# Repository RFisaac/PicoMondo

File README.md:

# PicoMondo

RP2350B control board for museum and maker exhibits (Clark Planetarium), designed in KiCad 10.

- `kicad/` is the project (`picomondo.kicad_pro`). Start with `kicad/README.md` and `kicad/DECISIONS.md`.
- `kicad/tools/` holds the Python scripts that generate and check the schematic and board.

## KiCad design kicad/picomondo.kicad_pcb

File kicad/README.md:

# PicoMondo KiCad project

Open `picomondo.kicad_pro` in KiCad 10. See [DECISIONS.md](DECISIONS.md) for what has been decided.
Reference designs and source material are in `../resources/`.

## Status

| Sheet | File | State |
|-------|------|-------|
| MCU core (RP2350B, regulator, crystal, flash, boot/reset, USB resistors, SWD) | `mcu_core.kicad_sch` | Done; all 80 MCU pin connections match the Pi minimal design |
| 5 V buck-boost (TPS55288) | `power_buck.kicad_sch` | Done, ERC clean (docs/power_buck_boost.md) |
| Power input (diode-OR, fuse, TVS, connectors) | `power_input.kicad_sch` | Done (docs/power_input.md) |
| 3.3 V regulators (AP2112K x2) | `power_ldo.kicad_sch` | Done (docs/power_ldo.md) |
| Switched outputs J7 / J8 / +5V_SW | `power_outputs.kicad_sch` | Done (docs/power_outputs.md) |
| USB-C + PD controller (STUSB4500) | `usb_pd.kicad_sch` | Done (docs/usb_pd.md) |
| EdgeLock connectors J1-J6, J9 | `io_edgelock.kicad_sch` | Done; real Molex footprints incl. board-edge notches (docs/io.md) |
| GPIO indicator LEDs | `io_indicators.kicad_sch` | Done |
| Arduino and Pico sockets | `io_headers.kicad_sch` | Done |
| microSD, WS2812, LEDs, pull-ups, test points, mounting | `io_misc.kicad_sch` | Done |
| PCB | `picomondo.kicad_pcb` | Created: outline, EdgeLock edge connectors, mounting holes, Arduino/Pico sockets placed; all parts imported, rest staged for you to place and route (docs/pcb.md) |

## How the schematic is built

Every part is placed explicitly and every connection is a pin stub ending in a net label or power
symbol, so net names (not wire routing) define the connections. GPIO, `RUN`, `USB_D+/-` and power
nets are global and join across sheets; other labels are local to their sheet.

`tools/` holds the generator and checkers:

| Script | Purpose |
|--------|---------|
| `build.py` | Creates the initial project files. **Overwrites** the schematics: do not run after editing in KiCad. |
| `kihelp.py`, `sheet_*.py` | Helper library and per-sheet definitions |
| `erc_report.py` | Runs KiCad ERC and prints a summary |
| `netlist.py` | Exports the netlist; `--ref U1`, `--net +3V3`, `--nets` |
| `compare_pi.py`, `compare_passives.py` | Check the MCU core against the Raspberry Pi reference |
| `make_pcb.py` | Creates the PCB once (needs KiCad's Python); see docs/pcb.md |
| `drc_report.py`, `project_settings.py` | PCB DRC summary; design rules and net classes |
| `place_edgelock_resistors.py` | Put each EdgeLock 100 ohm resistor in line with its pin |
| `place_swd_switches.py` | Place SWD header and BOOTSEL/RESET buttons at the right edge |
| `arrange_offboard.py` | Lay out the parts still off the board as labelled sub-circuit clusters |
| `place_rest.py` | Fit the remaining off-board parts into free space, near the parts they connect to |
| `place_usb_pd.py` | Place the USB-C PD support parts at J13 / U10 |
| `tp_to_back.py` | Flip the test points to the back |
| `place_mcu.py` | Place the RP2350B with its decoupling, regulator, crystal, flash and USB resistors |
| `place_gpio_indicators.py` | Continue each EdgeLock column with its 470 ohm and LED (LED beside the resistor, in an L) |
| `remove_led_jumpers.py` | Removed the ADC LED solder jumpers (schematic and board) |
| `add_shield_outlines.py` | Non-printing Uno and Pico outlines in the socket group |
| `apply_parts.py`, `sync_board_parts.py`, `bom.py` | LCSC numbers from `bom/parts.csv` into schematic and board; JLCPCB BOM, CPL and stock report |
| `fetch_datasheets.py`, `make_edgelock_fp.py`, `fix_lcsc_footprints.py`, `symfind.py`, `libpins.py` | Library and datasheet helpers |

Once a sheet has been edited in KiCad, that file is the source of truth. New sheets can be added
with the generator; edits to existing sheets should be made in KiCad or with kiutils
read-modify-write.

## Known ERC output

- `isolated_pin_label` on `GPIOn`: expected until the IO sheets exist.
- `lib_symbol_mismatch` on the crystal and flash: embedded copies differ cosmetically from the library.

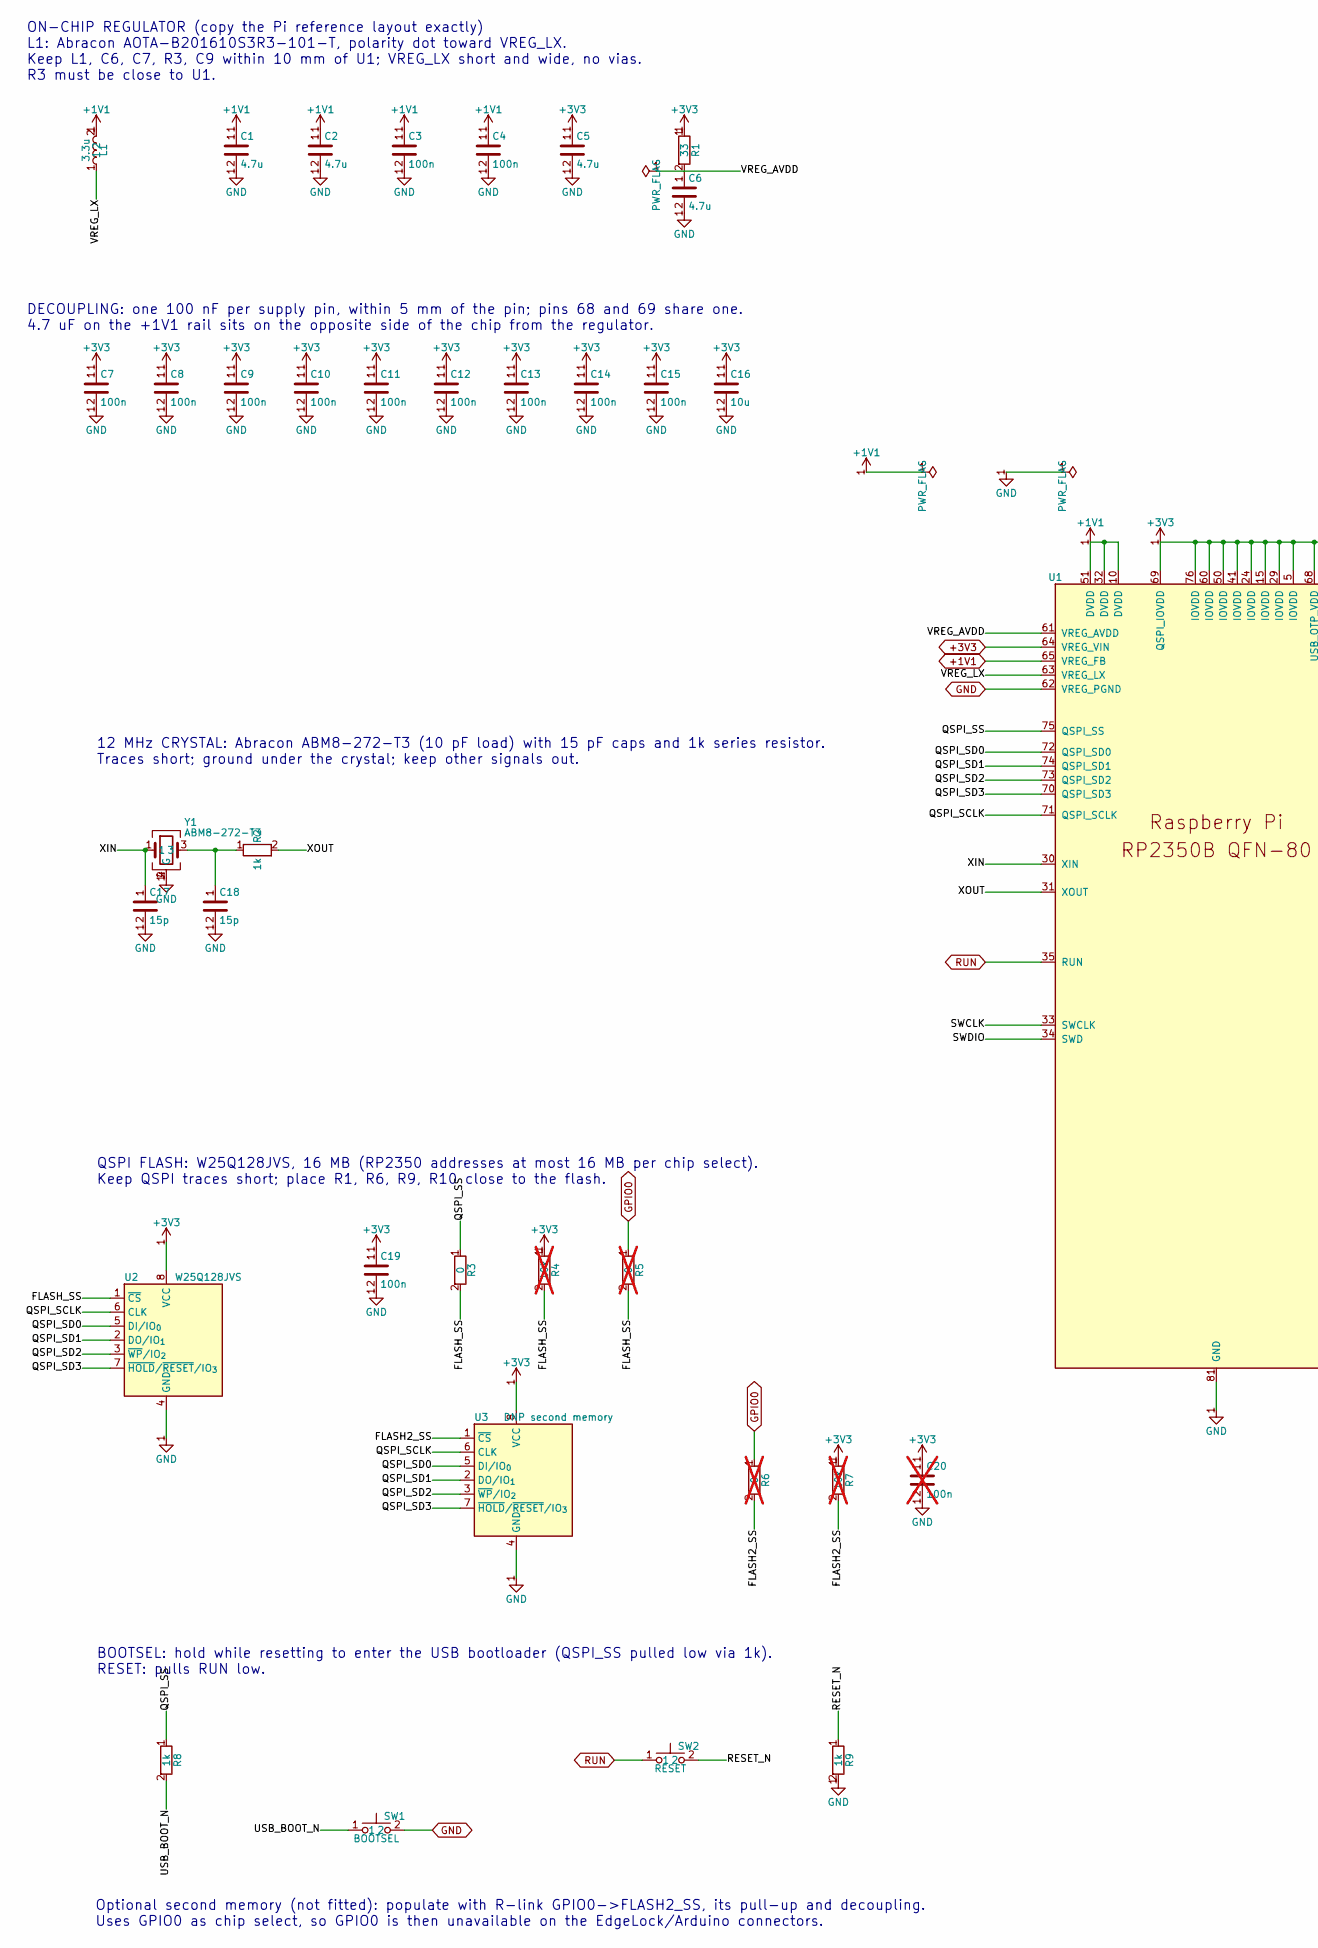
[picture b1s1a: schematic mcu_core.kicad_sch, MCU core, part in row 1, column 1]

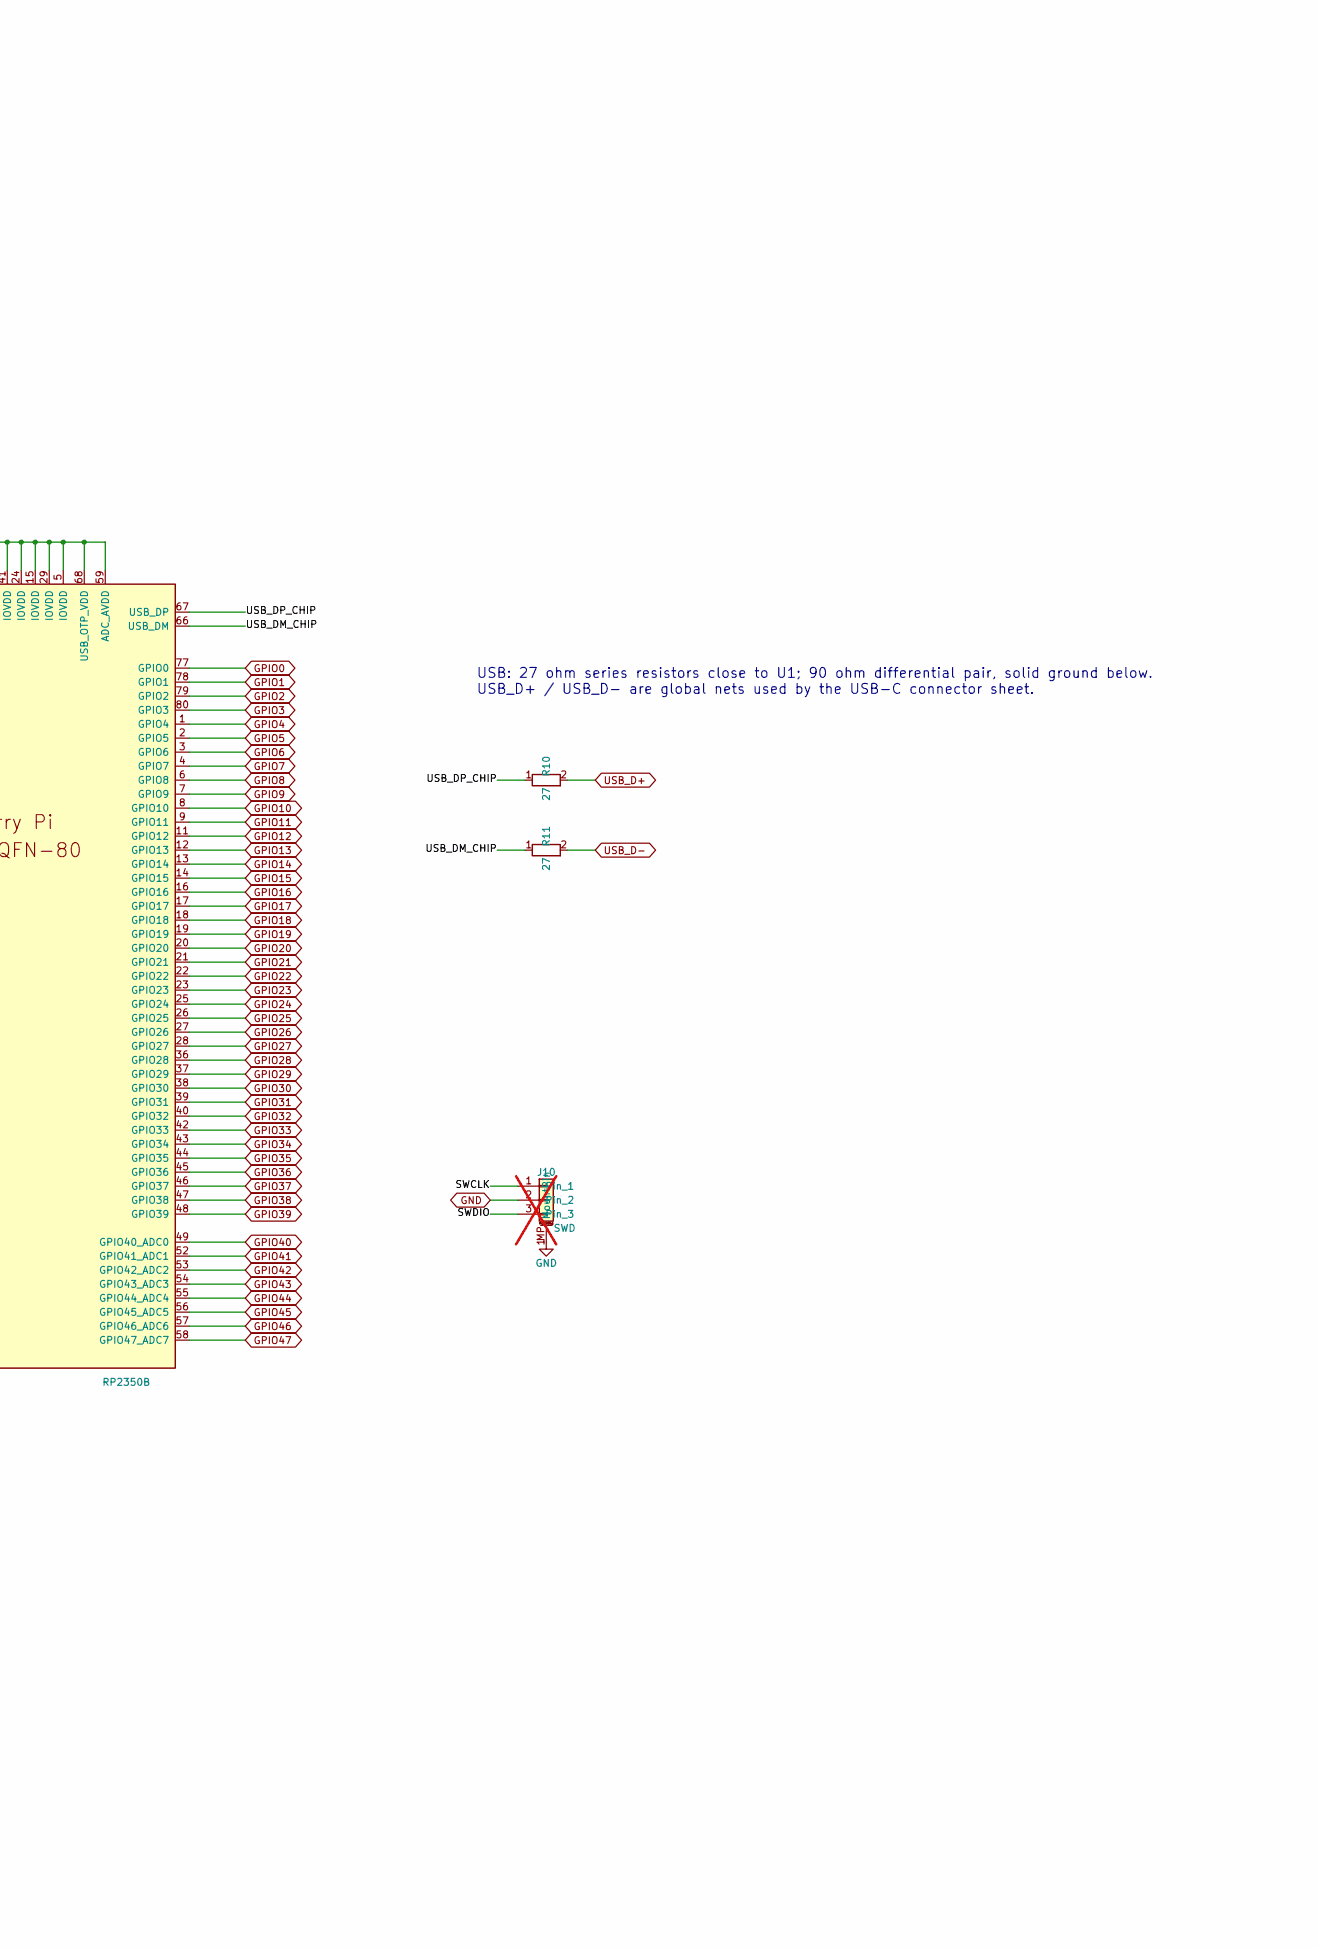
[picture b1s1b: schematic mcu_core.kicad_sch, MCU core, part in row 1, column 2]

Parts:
C1, C2, C5, C6: 4.7u; C_0402_1005Metric_small_pads; MPN CL05A475MP5NRNC; LCSC C23733
C3, C4, C7, C8, C9, C10, C11, C12, C13, C14, C15, C19: 100n; C_0402_1005Metric; MPN CL05B104KB54PNC; LCSC C307331
C16: 10u; C_0805_2012Metric; MPN CL21A106KAYNNNE; LCSC C15850
C17, C18: 15p; C_0402_1005Metric; MPN CC0402JRNPO9BN150; LCSC C106997
C20: 100n; C_0402_1005Metric; MPN CL05B104KB54PNC; LCSC C307331; not fitted
J10: SWD; PinHeader_1x03_P2.54mm_Horizontal; LCSC C239521; not fitted
L1: 3.3u; L_pol_2016; MPN AOTA-B201610S3R3-101-T; LCSC C42411119
R1: 33; R_0402_1005Metric; MPN 0402WGF330JTCE; LCSC C25105
R2, R8, R9: 1k; R_0402_1005Metric; MPN 0402WGF1001TCE; LCSC C11702
R3: 0; R_0402_1005Metric; MPN 0402WGF0000TCE; LCSC C17168
R4, R7: 10k; R_0402_1005Metric; MPN 0402WGF1002TCE; LCSC C25744; not fitted
R5, R6: 0; R_0402_1005Metric; MPN 0402WGF0000TCE; LCSC C17168; not fitted
R10, R11: 27; R_0402_1005Metric; MPN 0402WGF270JTCE; LCSC C25100
SW1: BOOTSEL; SW_SMD_TS-1187A_5.1x5.1; MPN TS-1187A-B-A-B; LCSC C318884
SW2: RESET; SW_SMD_TS-1187A_5.1x5.1; MPN TS-1187A-B-A-B; LCSC C318884
U1: RP2350B; RP2350-QFN-80-1EP_10x10_P0.4mm_EP3.4x3.4mm_ThermalVias; MPN RP2350B; LCSC C42415655
U2: W25Q128JVS; SOIC-8_5.3x5.3mm_P1.27mm; MPN W25Q128JVSIQ; LCSC C97521
U3: DNP second memory; SOIC-8_5.3x5.3mm_P1.27mm
Y1: ABM8-272-T3; Crystal_SMD_3225-4Pin_3.2x2.5mm; MPN ABM8-272-T3; LCSC C20625731

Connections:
+1V1: C1.1, C2.1, C3.1, C4.1, L1.2, U1.10 (DVDD), U1.32 (DVDD), U1.51 (DVDD), U1.65 (VREG_FB); also elsewhere on the board
+3V3: C5.1, C7.1, C8.1, C9.1, C10.1, C11.1, C12.1, C13.1, C14.1, C15.1, C16.1, C19.1, C20.1, R1.1, R4.1, R7.1, U1.5 (IOVDD), U1.15 (IOVDD), U1.24 (IOVDD), U1.29 (IOVDD), U1.41 (IOVDD), U1.50 (IOVDD), U1.59 (ADC_AVDD), U1.60 (IOVDD), U1.64 (VREG_VIN), U1.68 (USB_OTP_VDD), U1.69 (QSPI_IOVDD), U1.76 (IOVDD), U2.8 (VCC), U3.8 (VCC); also elsewhere on the board
/MCU core/FLASH2_SS: R6.2, R7.2, U3.1 (~CS)
/MCU core/FLASH_SS: R3.2, R4.2, R5.2, U2.1 (~CS)
/MCU core/QSPI_SCLK: U1.71 (QSPI_SCLK), U2.6 (CLK), U3.6 (CLK)
/MCU core/QSPI_SD0: U1.72 (QSPI_SD0), U2.5 (DI/IO_{0}), U3.5 (DI/IO_{0})
/MCU core/QSPI_SD1: U1.74 (QSPI_SD1), U2.2 (DO/IO_{1}), U3.2 (DO/IO_{1})
/MCU core/QSPI_SD2: U1.73 (QSPI_SD2), U2.3 (~WP/IO_{2}), U3.3 (~WP/IO_{2})
/MCU core/QSPI_SD3: U1.70 (QSPI_SD3), U2.7 (~HOLD/~RESET/IO_{3}), U3.7 (~HOLD/~RESET/IO_{3})
/MCU core/QSPI_SS: R3.1, R8.1, U1.75 (QSPI_SS)
/MCU core/RESET_N: R9.1, SW2.2
/MCU core/SWCLK: J10.1, U1.33 (SWCLK)
/MCU core/SWDIO: J10.3, U1.34 (SWD)
/MCU core/USB_BOOT_N: R8.2, SW1.1
/MCU core/USB_DM_CHIP: R11.1, U1.66 (USB_DM)
/MCU core/USB_DP_CHIP: R10.1, U1.67 (USB_DP)
/MCU core/VREG_AVDD: C6.1, R1.2, U1.61 (VREG_AVDD)
/MCU core/VREG_LX: L1.1, U1.63 (VREG_LX)
/MCU core/XIN: C17.1, U1.30 (XIN), Y1.1
/MCU core/XOUT: R2.2, U1.31 (XOUT)
GND: C1.2, C2.2, C3.2, C4.2, C5.2, C6.2, C7.2, C8.2, C9.2, C10.2, C11.2, C12.2, C13.2, C14.2, C15.2, C16.2, C17.2, C18.2, C19.2, C20.2, J10.2, J10.MP (MountPin), R9.2, SW1.2, U1.62 (VREG_PGND), U1.81 (GND), U2.4 (GND), U3.4 (GND), Y1.2 (G), Y1.4 (G); also elsewhere on the board
GPIO0: R5.1, R6.1, U1.77 (GPIO0); also elsewhere on the board
GPIO1: U1.78 (GPIO1); also elsewhere on the board
GPIO2: U1.79 (GPIO2); also elsewhere on the board
GPIO3: U1.80 (GPIO3); also elsewhere on the board
GPIO4: U1.1 (GPIO4); also elsewhere on the board
GPIO5: U1.2 (GPIO5); also elsewhere on the board
GPIO6: U1.3 (GPIO6); also elsewhere on the board
GPIO7: U1.4 (GPIO7); also elsewhere on the board
GPIO8: U1.6 (GPIO8); also elsewhere on the board
GPIO9: U1.7 (GPIO9); also elsewhere on the board
GPIO10: U1.8 (GPIO10); also elsewhere on the board
GPIO11: U1.9 (GPIO11); also elsewhere on the board
GPIO12: U1.11 (GPIO12); also elsewhere on the board
GPIO13: U1.12 (GPIO13); also elsewhere on the board
GPIO14: U1.13 (GPIO14); also elsewhere on the board
GPIO15: U1.14 (GPIO15); also elsewhere on the board
GPIO16: U1.16 (GPIO16); also elsewhere on the board
GPIO17: U1.17 (GPIO17); also elsewhere on the board
GPIO18: U1.18 (GPIO18); also elsewhere on the board
GPIO19: U1.19 (GPIO19); also elsewhere on the board
GPIO20: U1.20 (GPIO20); also elsewhere on the board
GPIO21: U1.21 (GPIO21); also elsewhere on the board
GPIO22: U1.22 (GPIO22); also elsewhere on the board
GPIO23: U1.23 (GPIO23); also elsewhere on the board
GPIO24: U1.25 (GPIO24); also elsewhere on the board
GPIO25: U1.26 (GPIO25); also elsewhere on the board
GPIO26: U1.27 (GPIO26); also elsewhere on the board
GPIO27: U1.28 (GPIO27); also elsewhere on the board
GPIO28: U1.36 (GPIO28); also elsewhere on the board
GPIO29: U1.37 (GPIO29); also elsewhere on the board
GPIO30: U1.38 (GPIO30); also elsewhere on the board
GPIO31: U1.39 (GPIO31); also elsewhere on the board
GPIO32: U1.40 (GPIO32); also elsewhere on the board
GPIO33: U1.42 (GPIO33); also elsewhere on the board
GPIO34: U1.43 (GPIO34); also elsewhere on the board
GPIO35: U1.44 (GPIO35); also elsewhere on the board
GPIO36: U1.45 (GPIO36); also elsewhere on the board
GPIO37: U1.46 (GPIO37); also elsewhere on the board
GPIO38: U1.47 (GPIO38); also elsewhere on the board
GPIO39: U1.48 (GPIO39); also elsewhere on the board
GPIO40: U1.49 (GPIO40_ADC0); also elsewhere on the board
GPIO41: U1.52 (GPIO41_ADC1); also elsewhere on the board
GPIO42: U1.53 (GPIO42_ADC2); also elsewhere on the board
GPIO43: U1.54 (GPIO43_ADC3); also elsewhere on the board
GPIO44: U1.55 (GPIO44_ADC4); also elsewhere on the board
GPIO45: U1.56 (GPIO45_ADC5); also elsewhere on the board
GPIO46: U1.57 (GPIO46_ADC6); also elsewhere on the board
GPIO47: U1.58 (GPIO47_ADC7); also elsewhere on the board
unnamed: C18.1, R2.1, Y1.3
RUN: SW2.1, U1.35 (RUN); also elsewhere on the board
USB_D+: R10.2; also elsewhere on the board
USB_D-: R11.2; also elsewhere on the board

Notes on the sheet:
BOOTSEL: hold while resetting to enter the USB bootloader (QSPI_SS pulled low via 1k). RESET: pulls RUN low.
12 MHz CRYSTAL: Abracon ABM8-272-T3 (10 pF load) with 15 pF caps and 1k series resistor. Traces short; ground under the crystal; keep other signals out.
ON-CHIP REGULATOR (copy the Pi reference layout exactly) L1: Abracon AOTA-B201610S3R3-101-T, polarity dot toward VREG_LX. Keep L1, C6, C7, R3, C9 within 10 mm of U1; VREG_LX short and wide, no vias. R3 must be close to U1.
Optional second memory (not fitted): populate with R-link GPIO0->FLASH2_SS, its pull-up and decoupling. Uses GPIO0 as chip select, so GPIO0 is then unavailable on the EdgeLock/Arduino connectors.
QSPI FLASH: W25Q128JVS, 16 MB (RP2350 addresses at most 16 MB per chip select). Keep QSPI traces short; place R1, R6, R9, R10 close to the flash.
DECOUPLING: one 100 nF per supply pin, within 5 mm of the pin; pins 68 and 69 share one. 4.7 uF on the +1V1 rail sits on the opposite side of the chip from the regulator.
USB: 27 ohm series resistors close to U1; 90 ohm differential pair, solid ground below. USB_D+ / USB_D- are global nets used by the USB-C connector sheet.

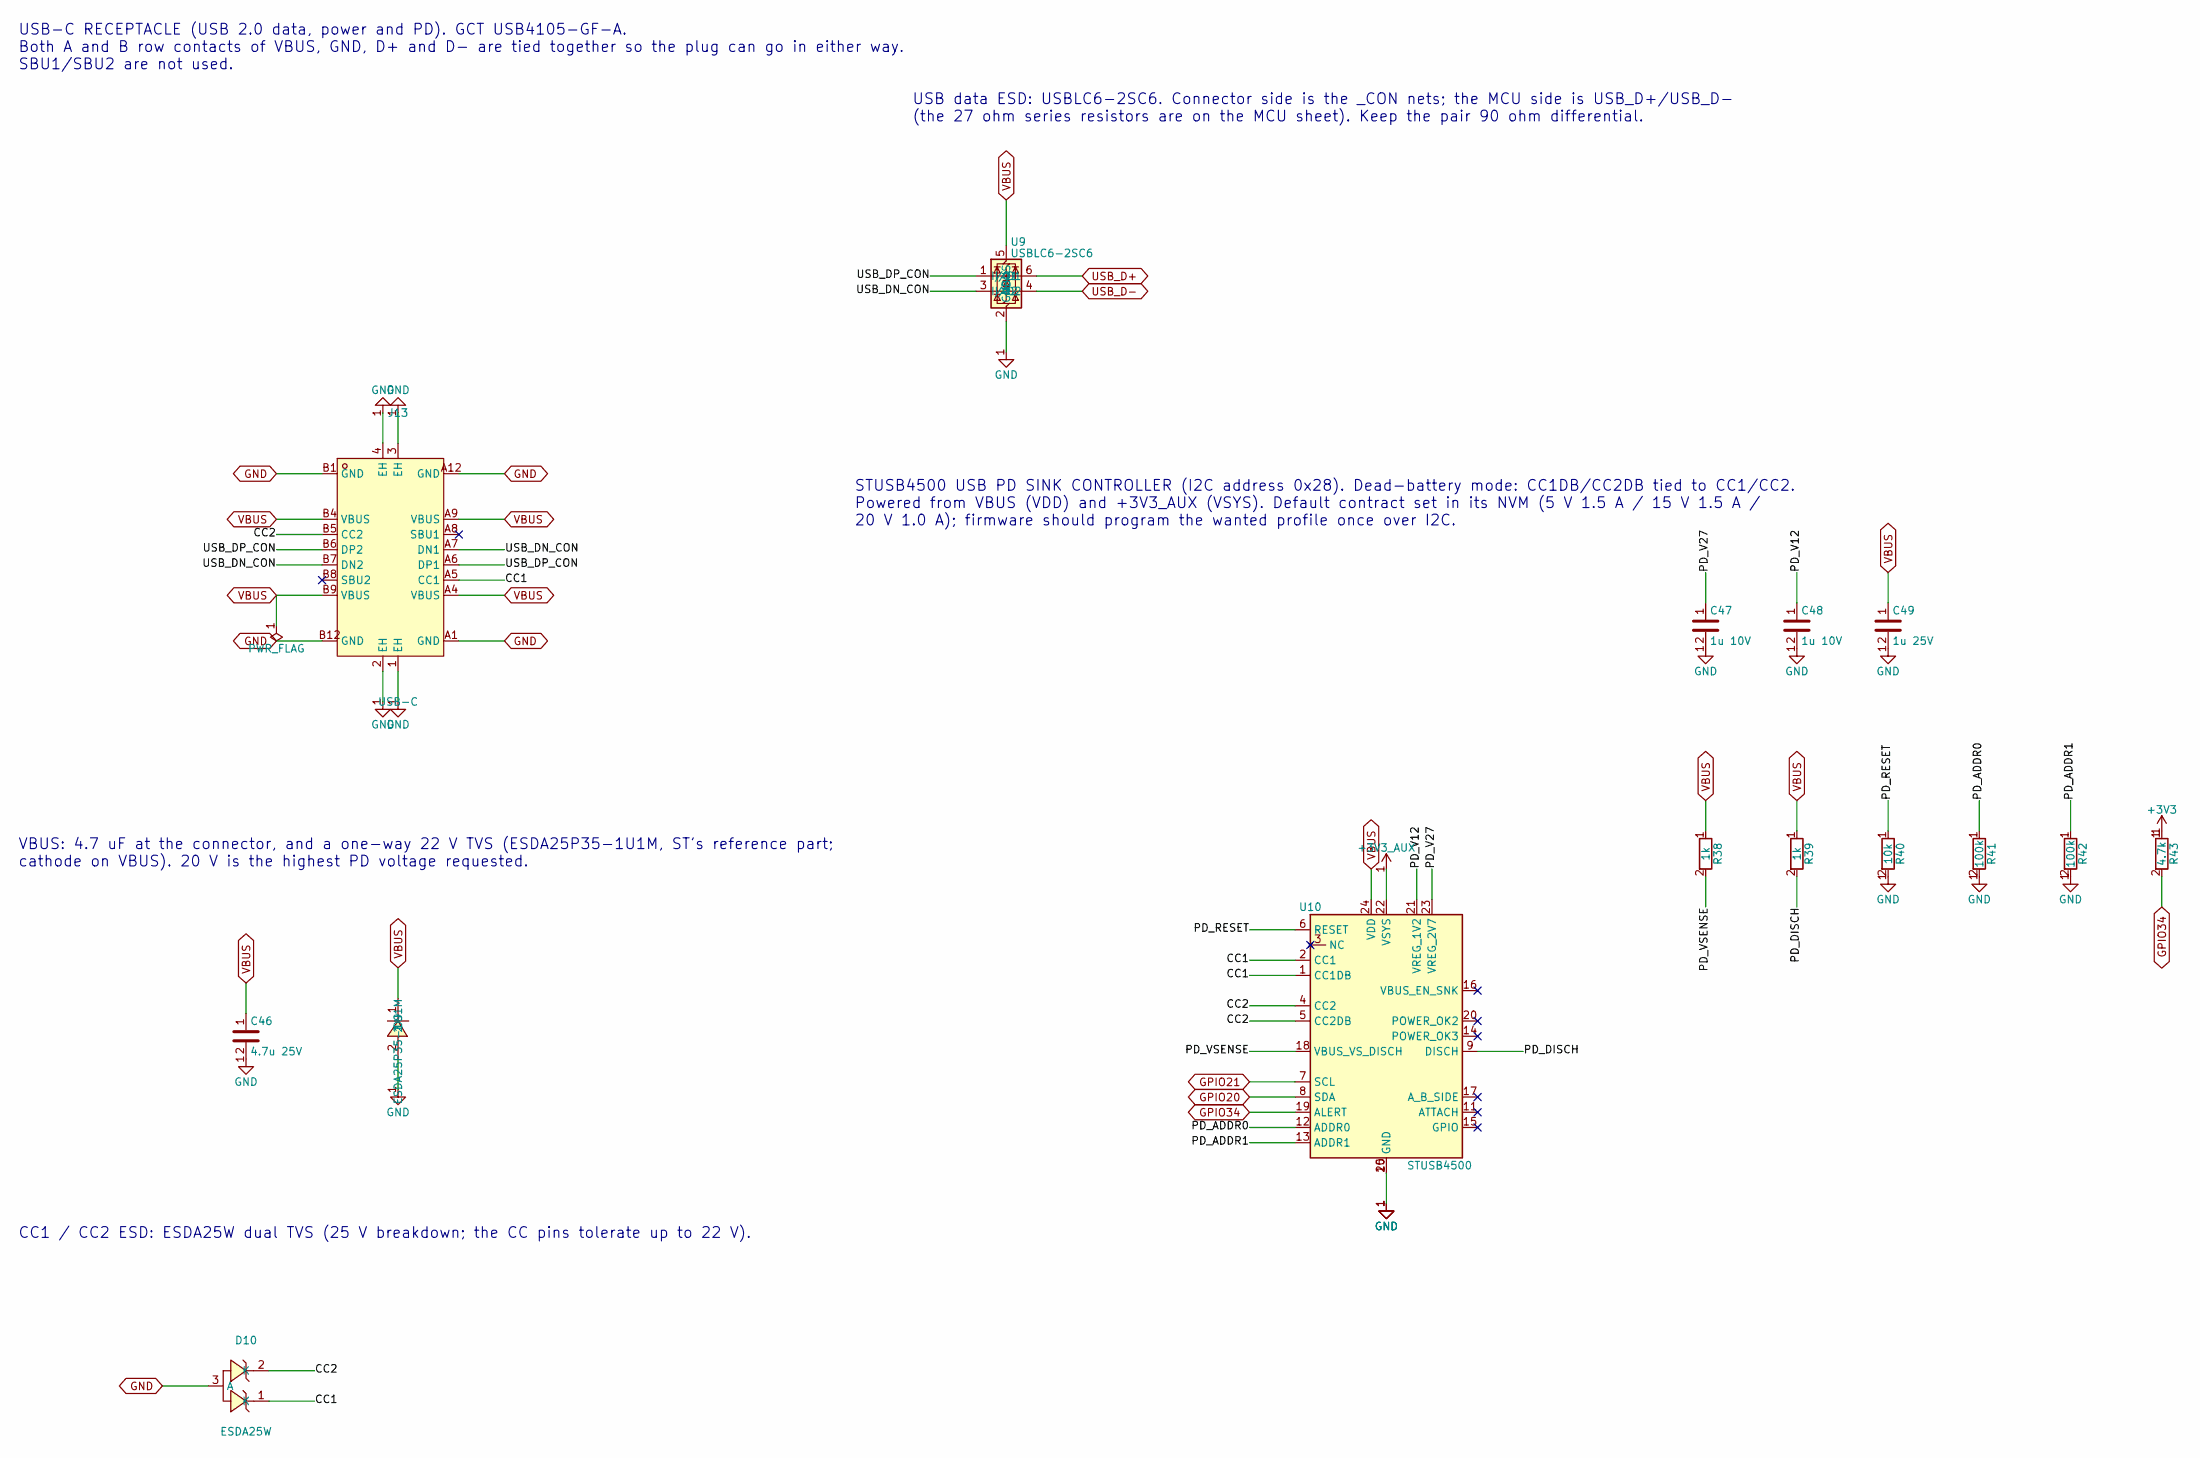
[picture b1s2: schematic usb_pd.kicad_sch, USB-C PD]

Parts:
C46: 4.7u 25V; C_0805_2012Metric; MPN CL21A475KAQNNNE; LCSC C1779
C47, C48: 1u 10V; C_0402_1005Metric; MPN CL05A105KA5NQNC; LCSC C52923
C49: 1u 25V; C_0603_1608Metric; MPN CL10A105KA8NNNC; LCSC C5673
D9: ESDA25P35-1U1M; DFN1610-2_L1.6-W1.0-P1.05-RD; MPN ESDA25P35-1U1M; LCSC C1974707
D10: ESDA25W; SOT-323-3_L2.1-W1.3-P1.32-LS2.1-BR; MPN ESDA25W; LCSC C2935152
J13: USB-C; TYPE-C-SMD_SBC-160S1A-20-S412; MPN USB4105-GF-A; LCSC C3020560
R38, R39: 1k; R_0402_1005Metric; MPN 0402WGF1001TCE; LCSC C11702
R40: 10k; R_0402_1005Metric; MPN 0402WGF1002TCE; LCSC C25744
R41, R42: 100k; R_0402_1005Metric; MPN 0402WGF1003TCE; LCSC C25741
R43: 4.7k; R_0402_1005Metric; MPN 0402WGF4701TCE; LCSC C25900
U9: USBLC6-2SC6; SOT-23-6; MPN USBLC6-2SC6; LCSC C7519
U10: STUSB4500; QFN-24-1EP_4x4mm_P0.5mm_EP2.7x2.7mm; MPN STUSB4500QTR; LCSC C2678061

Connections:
+3V3: R43.1; also elsewhere on the board
+3V3_AUX: U10.22 (VSYS); also elsewhere on the board
/USB-C PD/CC1: D10.1 (K), J13.A5 (CC1), U10.1 (CC1DB), U10.2 (CC1)
/USB-C PD/CC2: D10.2 (K), J13.B5 (CC2), U10.4 (CC2), U10.5 (CC2DB)
/USB-C PD/PD_ADDR0: R41.1, U10.12 (ADDR0)
/USB-C PD/PD_ADDR1: R42.1, U10.13 (ADDR1)
/USB-C PD/PD_DISCH: R39.2, U10.9 (DISCH)
/USB-C PD/PD_RESET: R40.1, U10.6 (RESET)
/USB-C PD/PD_V12: C48.1, U10.21 (VREG_1V2)
/USB-C PD/PD_V27: C47.1, U10.23 (VREG_2V7)
/USB-C PD/PD_VSENSE: R38.2, U10.18 (VBUS_VS_DISCH)
/USB-C PD/USB_DN_CON: J13.A7 (DN1), J13.B7 (DN2), U9.3 (I/O2)
/USB-C PD/USB_DP_CON: J13.A6 (DP1), J13.B6 (DP2), U9.1 (I/O1)
GND: C46.2, C47.2, C48.2, C49.2, D9.2, D10.3 (A), J13.1 (EH), J13.2 (EH), J13.3 (EH), J13.4 (EH), J13.A1 (GND), J13.A12 (GND), J13.B1 (GND), J13.B12 (GND), R40.2, R41.2, R42.2, U9.2 (GND), U10.10 (GND), U10.25 (GND); also elsewhere on the board
GPIO20: U10.8 (SDA); also elsewhere on the board
GPIO21: U10.7 (SCL); also elsewhere on the board
GPIO34: R43.2, U10.19 (ALERT); also elsewhere on the board
USB_D+: U9.6 (I/O1); also elsewhere on the board
USB_D-: U9.4 (I/O2); also elsewhere on the board
VBUS: C46.1, C49.1, D9.1, J13.A4 (VBUS), J13.A9 (VBUS), J13.B4 (VBUS), J13.B9 (VBUS), R38.1, R39.1, U9.5 (VBUS), U10.24 (VDD); also elsewhere on the board

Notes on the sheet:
VBUS: 4.7 uF at the connector, and a one-way 22 V TVS (ESDA25P35-1U1M, ST's reference part; cathode on VBUS). 20 V is the highest PD voltage requested.
USB data ESD: USBLC6-2SC6. Connector side is the _CON nets; the MCU side is USB_D+/USB_D- (the 27 ohm series resistors are on the MCU sheet). Keep the pair 90 ohm differential.
CC1 / CC2 ESD: ESDA25W dual TVS (25 V breakdown; the CC pins tolerate up to 22 V).
USB-C RECEPTACLE (USB 2.0 data, power and PD). GCT USB4105-GF-A. Both A and B row contacts of VBUS, GND, D+ and D- are tied together so the plug can go in either way. SBU1/SBU2 are not used.
STUSB4500 USB PD SINK CONTROLLER (I2C address 0x28). Dead-battery mode: CC1DB/CC2DB tied to CC1/CC2. Powered from VBUS (VDD) and +3V3_AUX (VSYS). Default contract set in its NVM (5 V 1.5 A / 15 V 1.5 A / 20 V 1.0 A); firmware should program the wanted profile once over I2C.

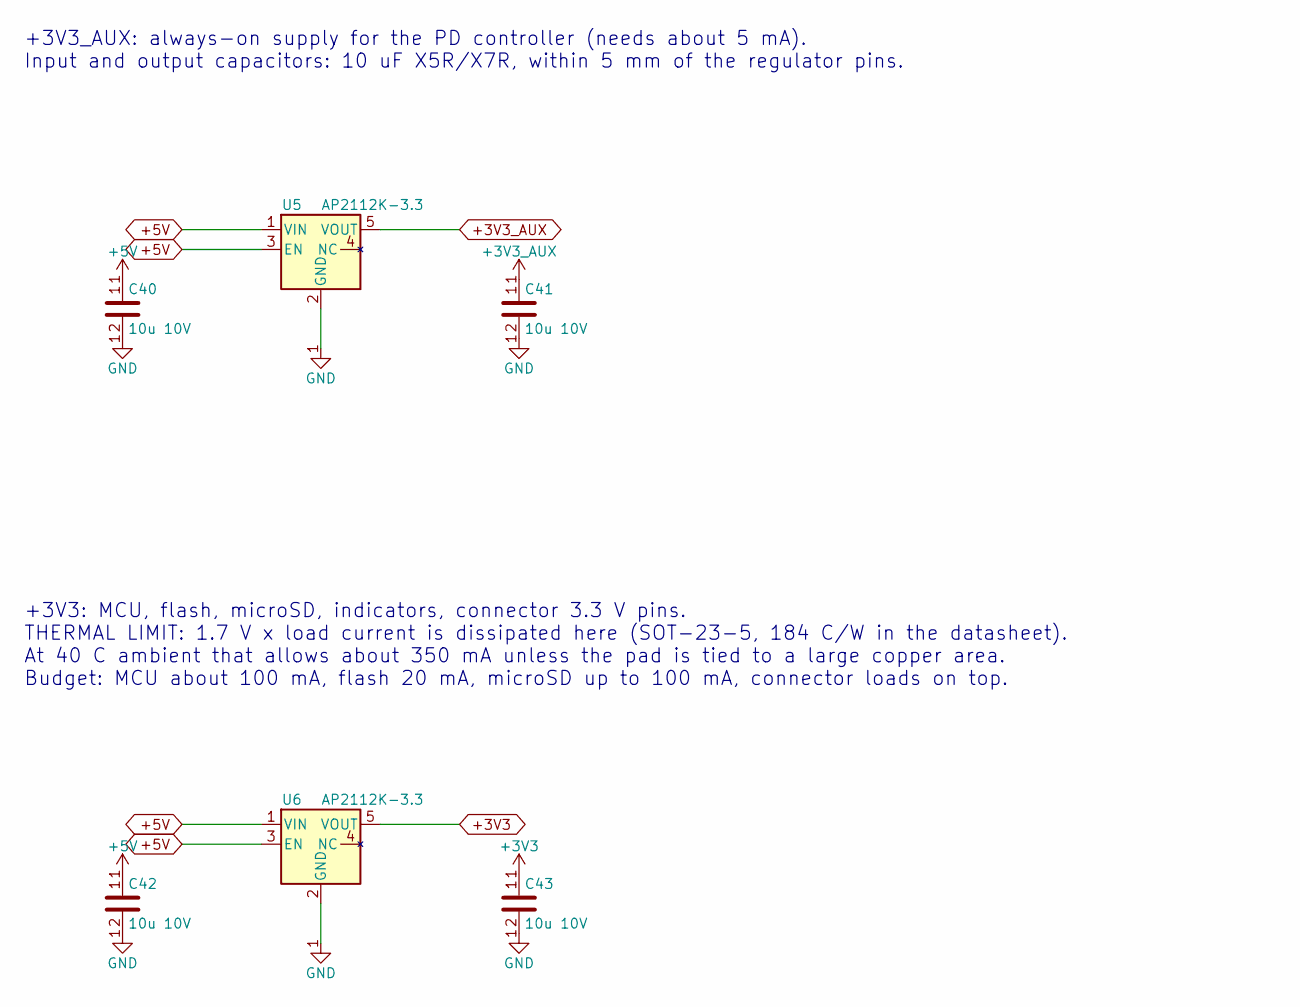
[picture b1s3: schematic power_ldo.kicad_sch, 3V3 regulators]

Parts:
C40, C41, C42, C43: 10u 10V; C_0805_2012Metric; MPN CL21A106KAYNNNE; LCSC C15850
U5, U6: AP2112K-3.3; SOT-23-5; MPN AP2112K-3.3TRG1; LCSC C51118

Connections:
+3V3: C43.1, U6.5 (VOUT); also elsewhere on the board
+3V3_AUX: C41.1, U5.5 (VOUT); also elsewhere on the board
+5V: C40.1, C42.1, U5.1 (VIN), U5.3 (EN), U6.1 (VIN), U6.3 (EN); also elsewhere on the board
GND: C40.2, C41.2, C42.2, C43.2, U5.2 (GND), U6.2 (GND); also elsewhere on the board

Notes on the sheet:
+3V3_AUX: always-on supply for the PD controller (needs about 5 mA). Input and output capacitors: 10 uF X5R/X7R, within 5 mm of the regulator pins.
+3V3: MCU, flash, microSD, indicators, connector 3.3 V pins. THERMAL LIMIT: 1.7 V x load current is dissipated here (SOT-23-5, 184 C/W in the datasheet). At 40 C ambient that allows about 350 mA unless the pad is tied to a large copper area. Budget: MCU about 100 mA, flash 20 mA, microSD up to 100 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

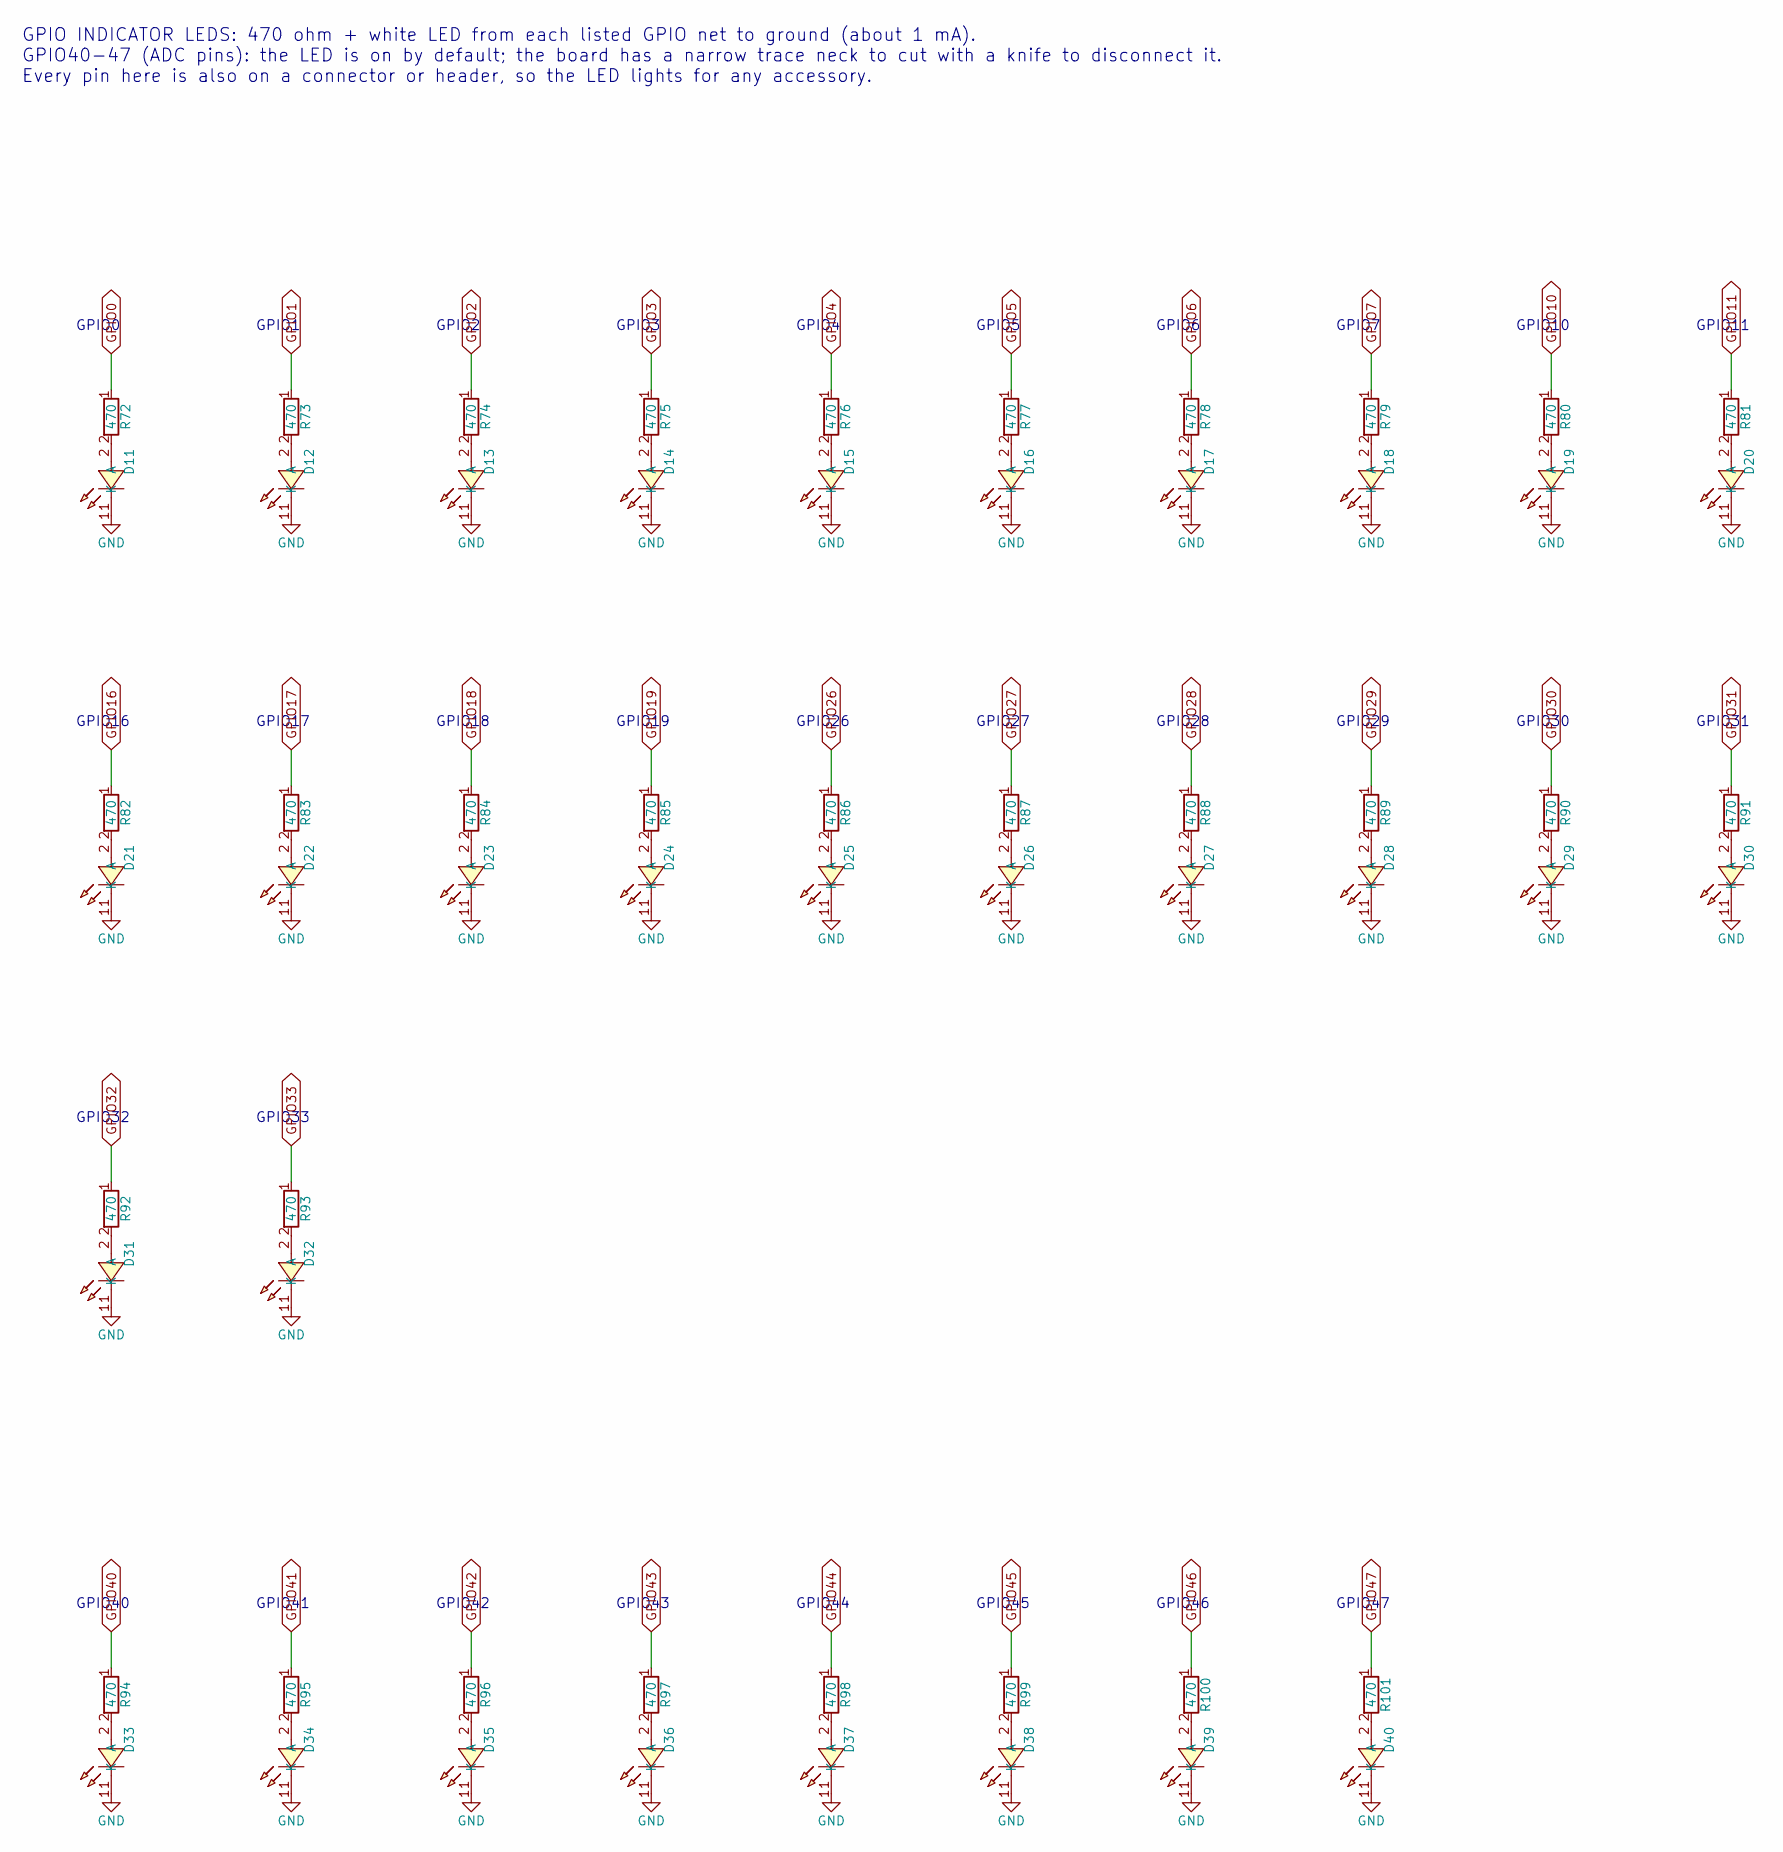
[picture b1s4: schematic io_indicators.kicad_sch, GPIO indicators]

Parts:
D11, D12, D13, D14, D15, D16, D17, D18, D19, D20, D21, D22, D23, D24, D25, D26, D27, D28, D29, D30, D31, D32, D33, D34, D35, D36, D37, D38, D39, D40: white; LED-SMD_L1.0-W0.5-RD_WHITE; MPN LW QH8G-Q2OO-3K5L-1; LCSC C7220928
R72, R73, R74, R75, R76, R77, R78, R79, R80, R81, R82, R83, R84, R85, R86, R87, R88, R89, R90, R91, R92, R93, R94, R95, R96, R97, R98, R99, R100, R101: 470; R_0402_1005Metric; MPN 0402WGF4700TCE; LCSC C25117

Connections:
GND: D11.1 (K), D12.1 (K), D13.1 (K), D14.1 (K), D15.1 (K), D16.1 (K), D17.1 (K), D18.1 (K), D19.1 (K), D20.1 (K), D21.1 (K), D22.1 (K), D23.1 (K), D24.1 (K), D25.1 (K), D26.1 (K), D27.1 (K), D28.1 (K), D29.1 (K), D30.1 (K), D31.1 (K), D32.1 (K), D33.1 (K), D34.1 (K), D35.1 (K), D36.1 (K), D37.1 (K), D38.1 (K), D39.1 (K), D40.1 (K); also elsewhere on the board
GPIO0: R72.1; also elsewhere on the board
GPIO1: R73.1; also elsewhere on the board
GPIO2: R74.1; also elsewhere on the board
GPIO3: R75.1; also elsewhere on the board
GPIO4: R76.1; also elsewhere on the board
GPIO5: R77.1; also elsewhere on the board
GPIO6: R78.1; also elsewhere on the board
GPIO7: R79.1; also elsewhere on the board
GPIO10: R80.1; also elsewhere on the board
GPIO11: R81.1; also elsewhere on the board
GPIO16: R82.1; also elsewhere on the board
GPIO17: R83.1; also elsewhere on the board
GPIO18: R84.1; also elsewhere on the board
GPIO19: R85.1; also elsewhere on the board
GPIO26: R86.1; also elsewhere on the board
GPIO27: R87.1; also elsewhere on the board
GPIO28: R88.1; also elsewhere on the board
GPIO29: R89.1; also elsewhere on the board
GPIO30: R90.1; also elsewhere on the board
GPIO31: R91.1; also elsewhere on the board
GPIO32: R92.1; also elsewhere on the board
GPIO33: R93.1; also elsewhere on the board
GPIO40: R94.1; also elsewhere on the board
GPIO41: R95.1; also elsewhere on the board
GPIO42: R96.1; also elsewhere on the board
GPIO43: R97.1; also elsewhere on the board
GPIO44: R98.1; also elsewhere on the board
GPIO45: R99.1; also elsewhere on the board
GPIO46: R100.1; also elsewhere on the board
GPIO47: R101.1; also elsewhere on the board
unnamed: D11.2 (A), R72.2
unnamed: D12.2 (A), R73.2
unnamed: D13.2 (A), R74.2
unnamed: D14.2 (A), R75.2
unnamed: D15.2 (A), R76.2
unnamed: D16.2 (A), R77.2
unnamed: D17.2 (A), R78.2
unnamed: D18.2 (A), R79.2
unnamed: D19.2 (A), R80.2
unnamed: D20.2 (A), R81.2
unnamed: D21.2 (A), R82.2
unnamed: D22.2 (A), R83.2
unnamed: D23.2 (A), R84.2
unnamed: D24.2 (A), R85.2
unnamed: D25.2 (A), R86.2
unnamed: D26.2 (A), R87.2
unnamed: D27.2 (A), R88.2
unnamed: D28.2 (A), R89.2
unnamed: D29.2 (A), R90.2
unnamed: D30.2 (A), R91.2
unnamed: D31.2 (A), R92.2
unnamed: D32.2 (A), R93.2
unnamed: D33.2 (A), R94.2
unnamed: D34.2 (A), R95.2
unnamed: D35.2 (A), R96.2
unnamed: D36.2 (A), R97.2
unnamed: D37.2 (A), R98.2
unnamed: D38.2 (A), R99.2
unnamed: D39.2 (A), R100.2
unnamed: D40.2 (A), R101.2

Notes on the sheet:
GPIO41
GPIO33
GPIO18
GPIO11
GPIO16
GPIO7
GPIO19
GPIO44
GPIO3
GPIO5
GPIO43
GPIO2
GPIO10
GPIO29
GPIO47
GPIO1
GPIO46
GPIO40
GPIO32
GPIO0
GPIO45
GPIO INDICATOR LEDS: 470 ohm + white LED from each listed GPIO net to ground (about 1 mA). GPIO40-47 (ADC pins): the LED is on by default; the board has a narrow trace neck to cut with a knife to disconnect it. Every pin here is also on a connector or header, so the LED lights for any accessory.
GPIO28
GPIO4
GPIO42
GPIO26
GPIO17
GPIO30
GPIO31
GPIO27
GPIO6
